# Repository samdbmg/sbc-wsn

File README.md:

# Speckled Bushcricket Wireless Sensor Network
Wireless Sensor Network for Acoustic Monitoring of Speckled Bush Crickets

##Known Issues (Node)
* Assembled sensor node temperature and light level sensors are broken (heat damage possibly)
* Sensor node environment sensors will require creative mounting for light and RH to be exposed outside. Suggest modifying onto an external header to another board (would also solve above problem)

##Known Issues (Base)
* GSM Modem doesn't currently execute HTTP requests, an error returns after setting the URL
* Base unit sometimes doesn't wake up at same time as node. Fitting a crystal to the Discovery board and switching RTC to the external 32k oscillator may help
* Power supplies start and generate stable output, however destroy regulator ICs after Discovery board is connected. Recommend thorough design review
* Discovery board will not fit unless headphone connector and button caps are removed. Suggest reworking to flip board, so Discovery fits on top and modem on bottom

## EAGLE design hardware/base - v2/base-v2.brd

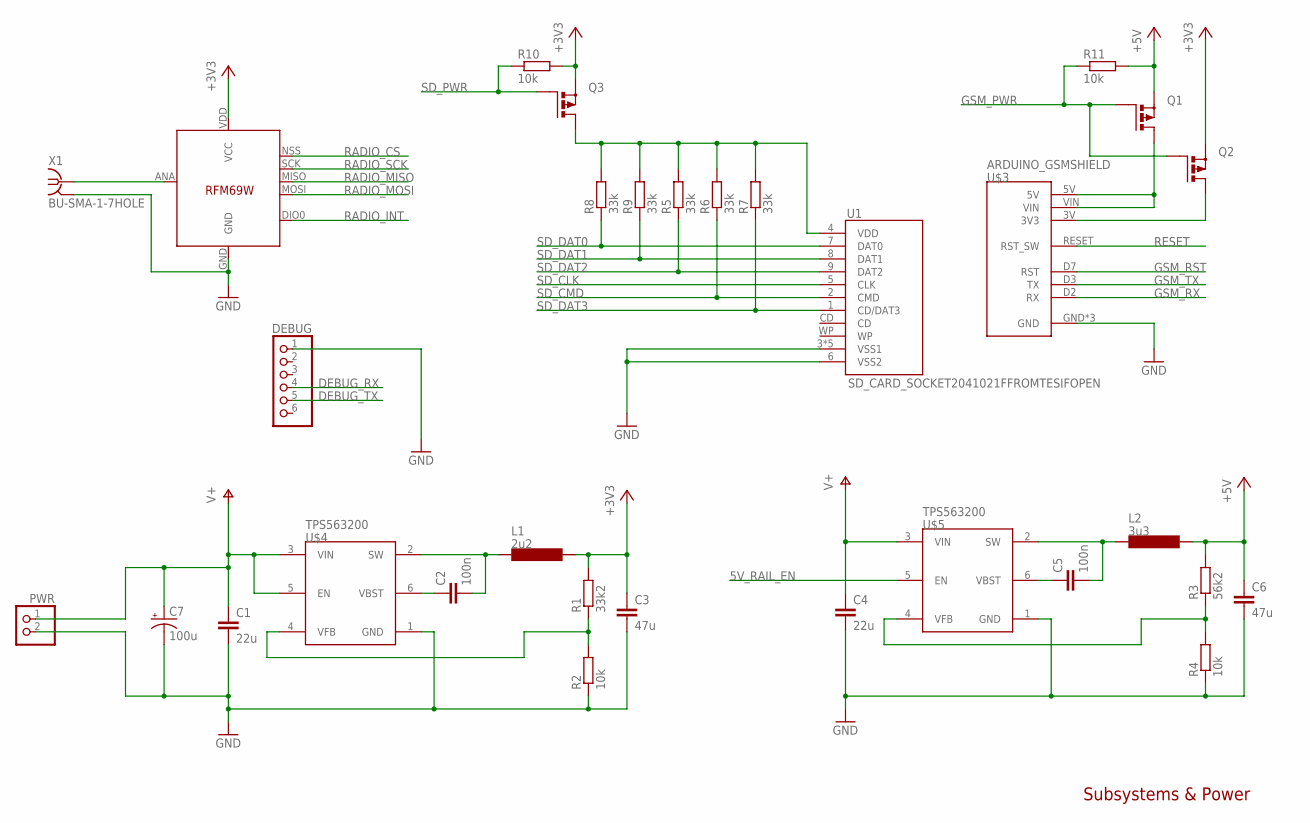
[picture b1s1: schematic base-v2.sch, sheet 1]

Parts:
C1, C4: 22u; 1206
C2, C5: 100n; CAP-PTH-SMALL
C3, C6: 47u; 1206
C7: 100u; CPOL-RADIAL-10UF-25V
DEBUG: PINHD-1X6; 1X06
L1: 2u2; SRR7032
L2: 3u3; SRR7032
PWR: PINHD-1X2; 1X02
Q1, Q2, Q3: PMOSFET_PTO220BH; TO220BH
R1: 33k2; 0204/7
R2, R4, R10, R11: 10k; 0204/7
R3: 56k2; 0204/7
R5, R6, R7, R8, R9: 33k; 0204/7
U1: SD_CARD_SOCKET2041021FFROMTESIFOPEN; SDCARD_2041021-3
U$2: RFM69; RFM69W-MINPADS
U$3: ARDUINO_GSMSHIELD; ARDUINO-NOHOLE
U$4, U$5: TPS563200; DDC0006A
X1: BU-SMA-1-7HOLE; SMA_1-7HOLES

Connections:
5V_RAIL_EN: U$5.5 (EN); also elsewhere on the board
+3V3: C3.1, L1.2, Q2.S, Q3.S, R1.2, R10.2, U$2.VDD (VCC); also elsewhere on the board
+5V: C6.1, L2.2, Q1.S, R3.2, R11.2; also elsewhere on the board
DEBUG_RX: DEBUG.4; also elsewhere on the board
DEBUG_TX: DEBUG.5; also elsewhere on the board
GND: C1.2, C3.2, C4.2, C6.2, C7.2 (-), DEBUG.1, PWR.2, R2.1, R4.1, U1.3 (VSS1), U1.6 (VSS2), U1.SH1 (VSS1), U1.SH2 (VSS1), U1.SH3 (VSS1), U1.SH4 (VSS1), U$2.GND, U$3.GND, U$3.GND1 (GND), U$3.GND2 (GND), U$4.1 (GND), U$5.1 (GND), X1.2, X1.3 (2), X1.4 (2), X1.5 (2); also elsewhere on the board
GSM_PWR: Q1.G, Q2.G, R11.1; also elsewhere on the board
GSM_RST: U$3.D7 (RST); also elsewhere on the board
GSM_RX: U$3.D2 (RX); also elsewhere on the board
GSM_TX: U$3.D3 (TX); also elsewhere on the board
unnamed: Q1.D, U$3.5V, U$3.VIN
unnamed: Q2.D, U$3.3V (3V3)
RADIO_ANT: U$2.ANA (ANT), X1.1
RADIO_CS: U$2.NSS (SEL); also elsewhere on the board
RADIO_INT: U$2.DIO0; also elsewhere on the board
RADIO_MISO: U$2.MISO; also elsewhere on the board
RADIO_MOSI: U$2.MOSI; also elsewhere on the board
RADIO_SCK: U$2.SCK; also elsewhere on the board
RESET: U$3.RESET (RST_SW); also elsewhere on the board
SD_CLK: U1.5 (CLK); also elsewhere on the board
SD_CMD: R6.1, U1.2 (CMD); also elsewhere on the board
SD_DAT0: R8.1, U1.7 (DAT0); also elsewhere on the board
SD_DAT1: R9.1, U1.8 (DAT1); also elsewhere on the board
SD_DAT2: R5.1, U1.9 (DAT2); also elsewhere on the board
SD_DAT3: R7.1, U1.1 (CD/DAT3); also elsewhere on the board
SD_PWR: Q3.G, R10.1; also elsewhere on the board
SD_VCC: Q3.D, R5.2, R6.2, R7.2, R8.2, R9.2, U1.4 (VDD)
V+: C1.1, C4.1, C7.1 (+), PWR.1, U$4.3 (VIN), U$4.5 (EN), U$5.3 (VIN)
VREG_3_SW: C2.2, L1.1, U$4.2 (SW)
VREG_3_VBST: C2.1, U$4.6 (VBST)
VREG_3_VFB: R1.1, R2.2, U$4.4 (VFB)
VREG_5_SW: C5.2, L2.1, U$5.2 (SW)
VREG_5_VBST: C5.1, U$5.6 (VBST)
VREG_5_VFB: R3.1, R4.2, U$5.4 (VFB)

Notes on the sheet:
Subsystems & Power

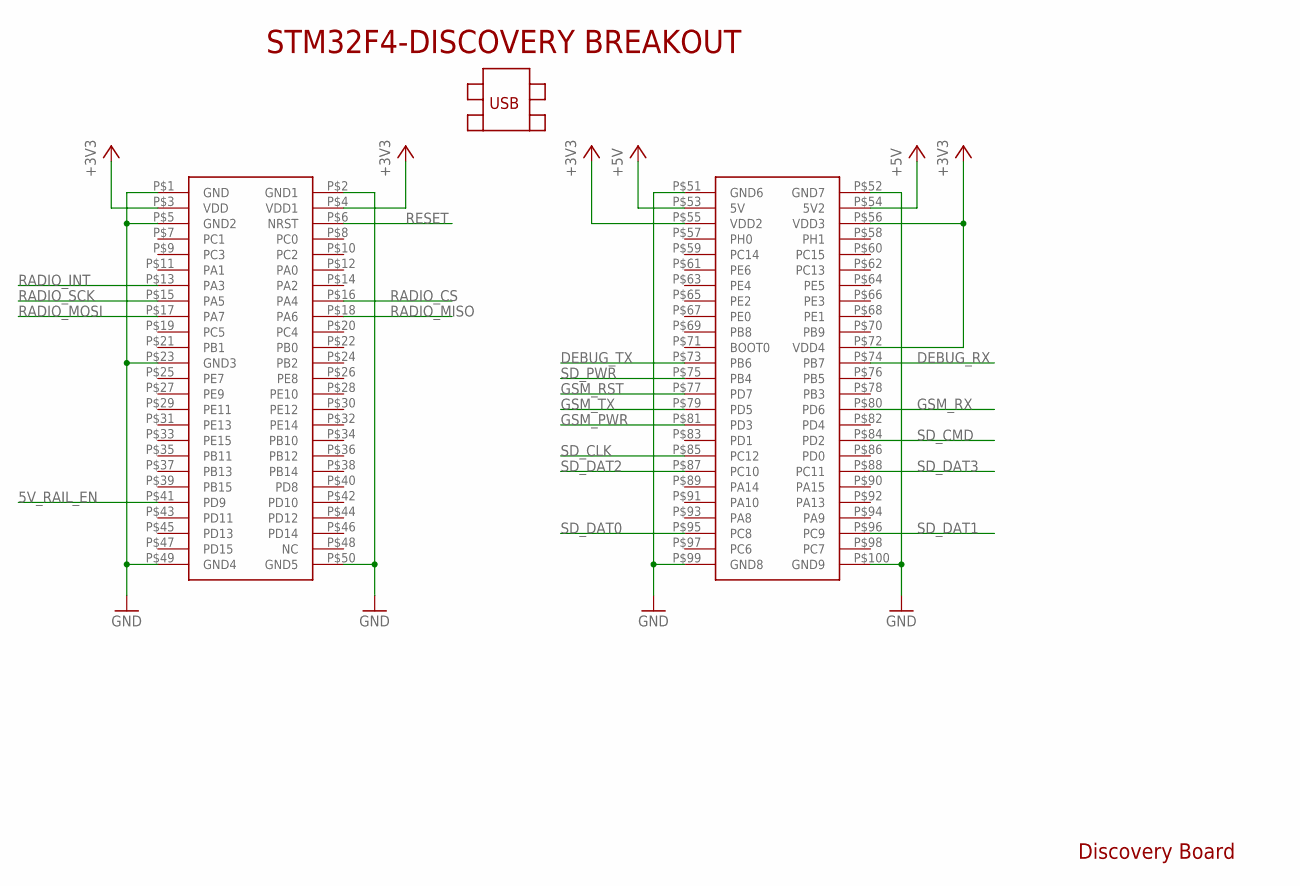
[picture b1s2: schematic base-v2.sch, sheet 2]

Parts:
U$1: STM32F4-DISCOVERY

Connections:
5V_RAIL_EN: U$1.P$41 (PD9); also elsewhere on the board
+3V3: U$1.P$3 (VDD), U$1.P$4 (VDD1), U$1.P$55 (VDD2), U$1.P$56 (VDD3), U$1.P$72 (VDD4); also elsewhere on the board
+5V: U$1.P$53 (5V), U$1.P$54 (5V2); also elsewhere on the board
DEBUG_RX: U$1.P$74 (PB7); also elsewhere on the board
DEBUG_TX: U$1.P$73 (PB6); also elsewhere on the board
GND: U$1.P$1 (GND), U$1.P$2 (GND1), U$1.P$5 (GND2), U$1.P$23 (GND3), U$1.P$49 (GND4), U$1.P$50 (GND5), U$1.P$51 (GND6), U$1.P$52 (GND7), U$1.P$99 (GND8), U$1.P$100 (GND9); also elsewhere on the board
GSM_PWR: U$1.P$81 (PD3); also elsewhere on the board
GSM_RST: U$1.P$77 (PD7); also elsewhere on the board
GSM_RX: U$1.P$80 (PD6); also elsewhere on the board
GSM_TX: U$1.P$79 (PD5); also elsewhere on the board
RADIO_CS: U$1.P$16 (PA4); also elsewhere on the board
RADIO_INT: U$1.P$13 (PA3); also elsewhere on the board
RADIO_MISO: U$1.P$18 (PA6); also elsewhere on the board
RADIO_MOSI: U$1.P$17 (PA7); also elsewhere on the board
RADIO_SCK: U$1.P$15 (PA5); also elsewhere on the board
RESET: U$1.P$6 (NRST); also elsewhere on the board
SD_CLK: U$1.P$85 (PC12); also elsewhere on the board
SD_CMD: U$1.P$84 (PD2); also elsewhere on the board
SD_DAT0: U$1.P$95 (PC8); also elsewhere on the board
SD_DAT1: U$1.P$96 (PC9); also elsewhere on the board
SD_DAT2: U$1.P$87 (PC10); also elsewhere on the board
SD_DAT3: U$1.P$88 (PC11); also elsewhere on the board
SD_PWR: U$1.P$75 (PB4); also elsewhere on the board

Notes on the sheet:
Discovery Board

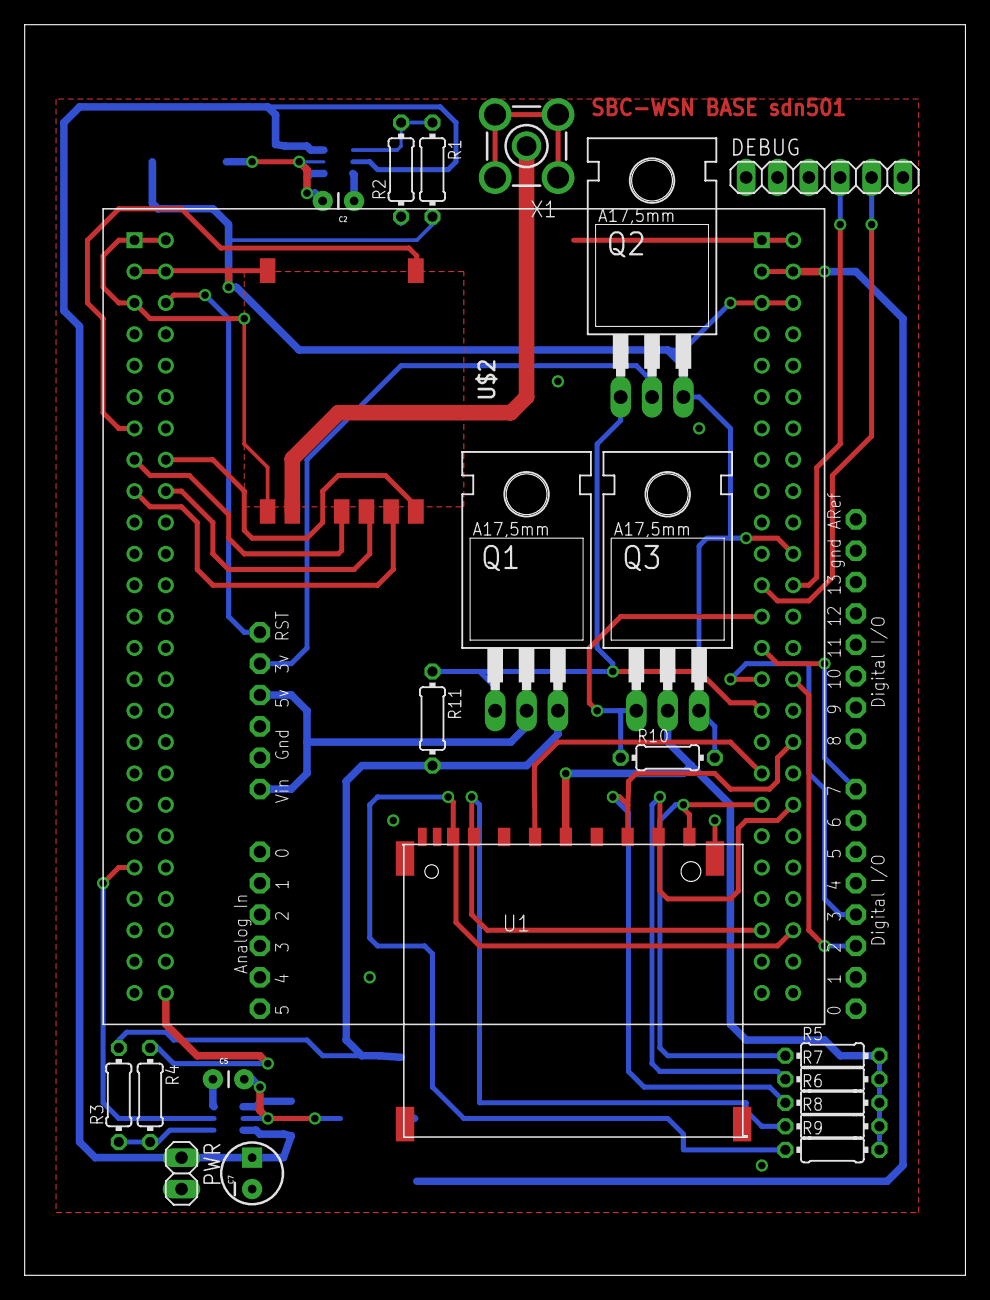
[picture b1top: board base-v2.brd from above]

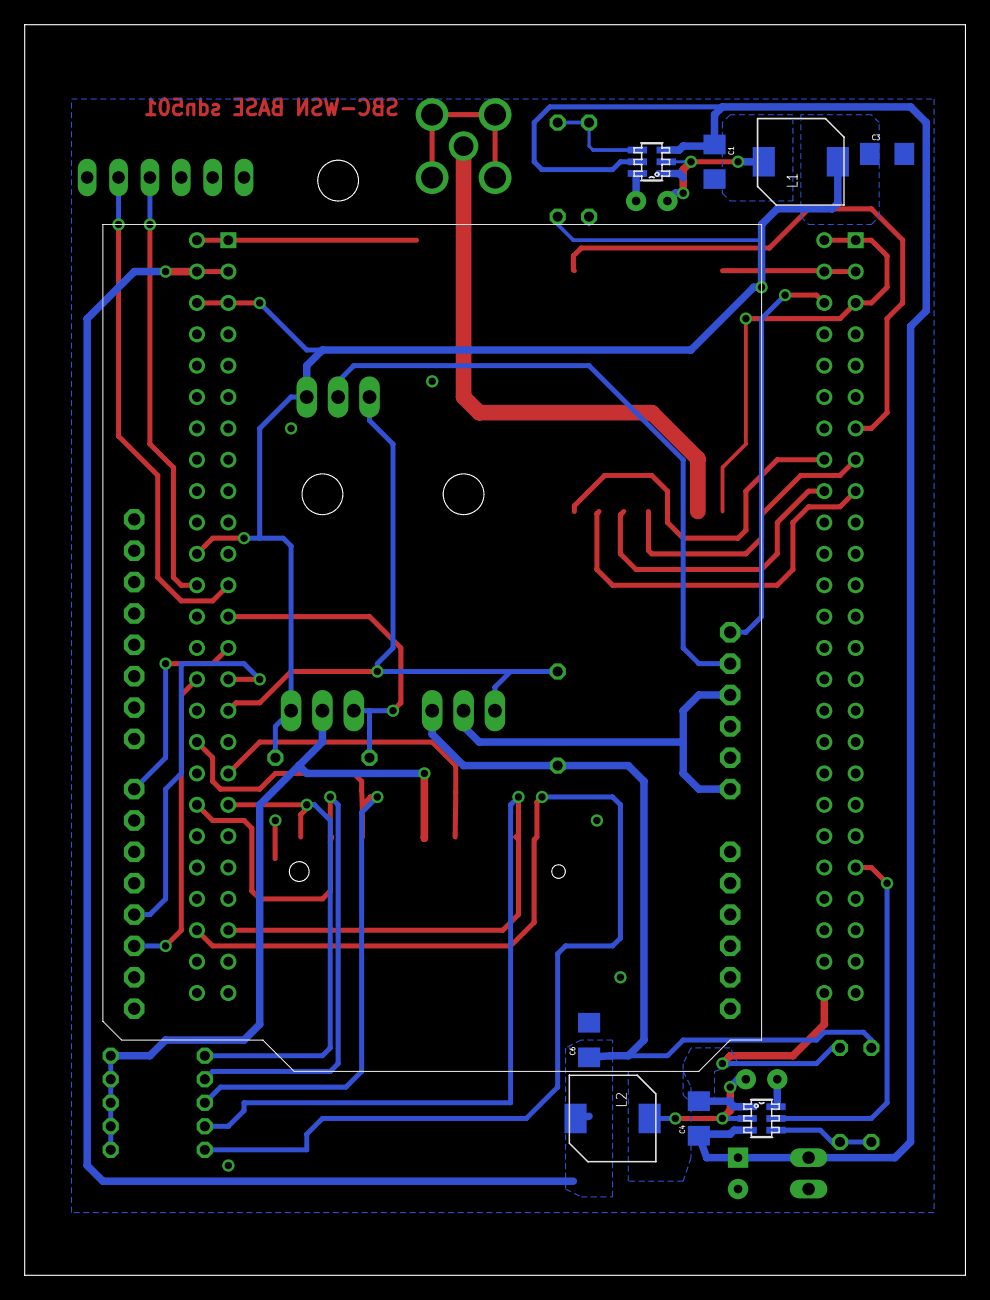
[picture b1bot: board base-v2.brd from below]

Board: 2 copper layers, 76.2 x 101.3 mm, 32 parts (8 on the bottom side), 34 nets.

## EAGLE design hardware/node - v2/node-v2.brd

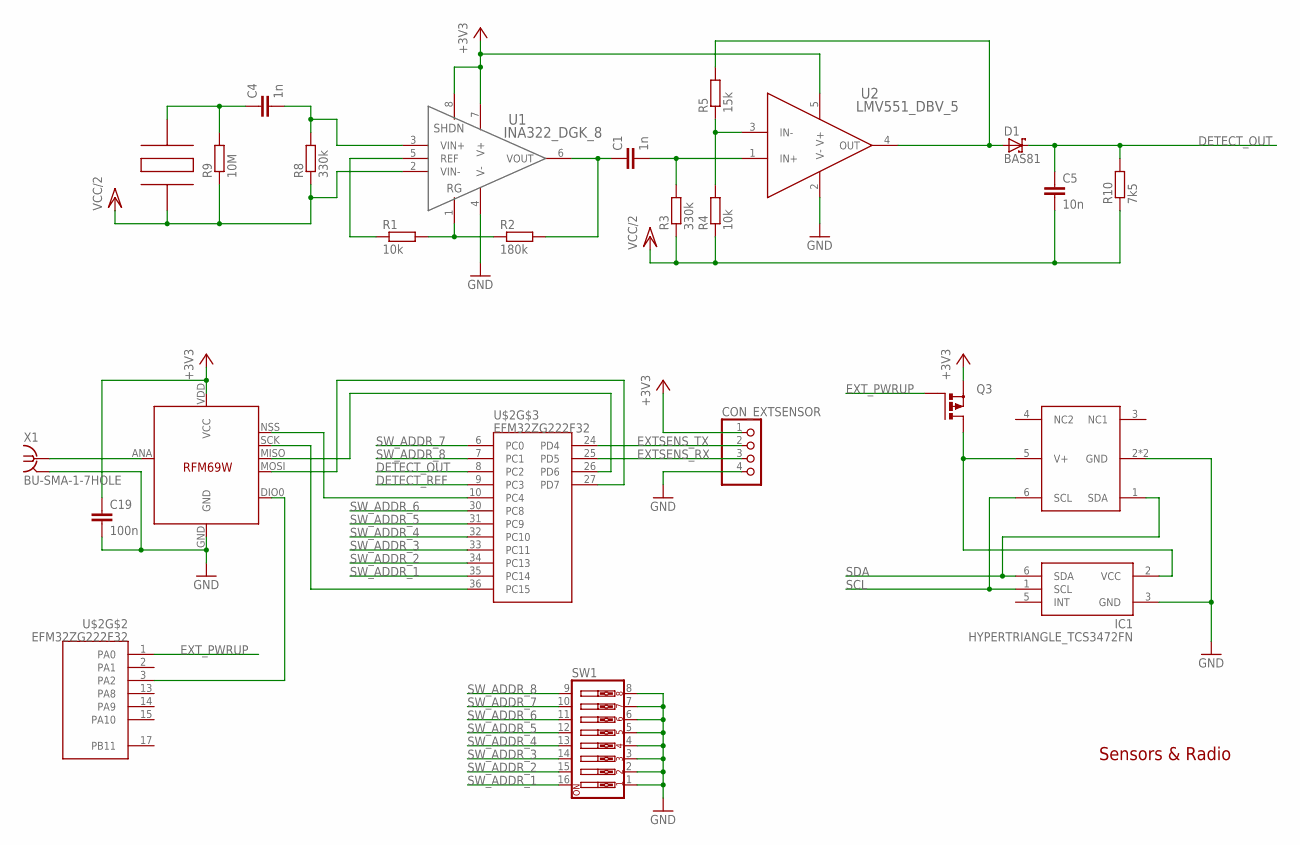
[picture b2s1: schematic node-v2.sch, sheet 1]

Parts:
C1, C4: 1n; CAP-PTH-SMALL
C5: 10n; CAP-PTH-SMALL
C19: 100n; CAP-PTH-SMALL
CON_EXTSENSOR: PINHD-1X4; 1X04
D1: BAS81; DO35-7
IC1: HYPERTRIANGLE_TCS3472FN; HYPERTRIANGLE_DFN-6
Q3: PMOSFET_PTO220BH; TO220BH
R1, R4: 10k; 0204/7
R2: 180k; 0204/7
R3, R8: 330k; 0204/7
R5: 15k; 0204/7
R9: 10M; 0204/7
R10: 7k5; 0204/7
RADIO: RFM69; RFM69W-MINPADS
SW1: SW_DIP-8; DIPSWITCH-08
U1: INA322_DGK_8; DGK8
U2: LMV551_DBV_5; MF05A
U$1: PIEZOWIREHEADER; 1X02
U$2: EFM32ZG222F32; QFP48
U$3: SHT21
X1: BU-SMA-1-7HOLE; SMA_1-7HOLES

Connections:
+3V3: C19.1, CON_EXTSENSOR.1, Q3.S, RADIO.VDD (VCC), U1.7 (V+), U1.8 (SHDN), U2.5 (V+); also elsewhere on the board
DETECT_OUT: C5.1, D1.C, R10.2, U$2.8 (PC2)
DETECT_REF: U$2.9 (PC3); also elsewhere on the board
EXTSENS_RX: CON_EXTSENSOR.3, U$2.25 (PD5)
EXTSENS_TX: CON_EXTSENSOR.2, U$2.24 (PD4)
EXT_PWRLINE: IC1.2 (VCC), Q3.D, U$3.5 (V+)
EXT_PWRUP: Q3.G, U$2.1 (PA0)
GND: C19.2, CON_EXTSENSOR.4, IC1.3 (GND), RADIO.GND, SW1.1, SW1.2, SW1.3, SW1.4, SW1.5, SW1.6, SW1.7, SW1.8, U1.4 (V-), U2.2 (V-), U$3.2 (GND), U$3.P$1 (GND), X1.2, X1.3 (2), X1.4 (2), X1.5 (2); also elsewhere on the board
INSTR_FILTERED: C1.2, R3.2, U2.1 (IN+)
INSTR_OUT: C1.1, R2.2, U1.6 (VOUT)
unnamed: RADIO.MISO, U$2.26 (PD6)
OPAMP_OUT: D1.A, R5.2, U2.4 (OUT)
OPAMP_VGND: R4.2, R5.1, U2.3 (IN-)
PIEZO_FILTERED: C4.2, R8.2, U1.3 (VIN+)
PIEZO_OUT: C4.1, R9.2, U$1.1 (S+)
RADIO_ANT: RADIO.ANA (ANT), X1.1
RADIO_CS: RADIO.NSS (SEL), U$2.10 (PC4)
RADIO_INT: RADIO.DIO0, U$2.3 (PA2)
RADIO_MOSI: RADIO.MOSI, U$2.27 (PD7)
RADIO_SCK: RADIO.SCK, U$2.36 (PC15)
REFLINE: R1.1, U1.5 (REF)
RGLINE: R1.2, R2.1, U1.1 (RG)
SCL: IC1.1 (SCL), U$3.6 (SCL); also elsewhere on the board
SDA: IC1.6 (SDA), U$3.1 (SDA); also elsewhere on the board
SW_ADDR_1: SW1.16, U$2.35 (PC14)
SW_ADDR_2: SW1.15, U$2.34 (PC13)
SW_ADDR_3: SW1.14, U$2.33 (PC11)
SW_ADDR_4: SW1.13, U$2.32 (PC10)
SW_ADDR_5: SW1.12, U$2.31 (PC9)
SW_ADDR_6: SW1.11, U$2.30 (PC8)
SW_ADDR_7: SW1.10, U$2.6 (PC0)
SW_ADDR_8: SW1.9, U$2.7 (PC1)
VCC/2: C5.2, R3.1, R4.1, R8.1, R9.1, R10.1, U1.2 (VIN-), U$1.2 (S-); also elsewhere on the board

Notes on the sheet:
Sensors & Radio

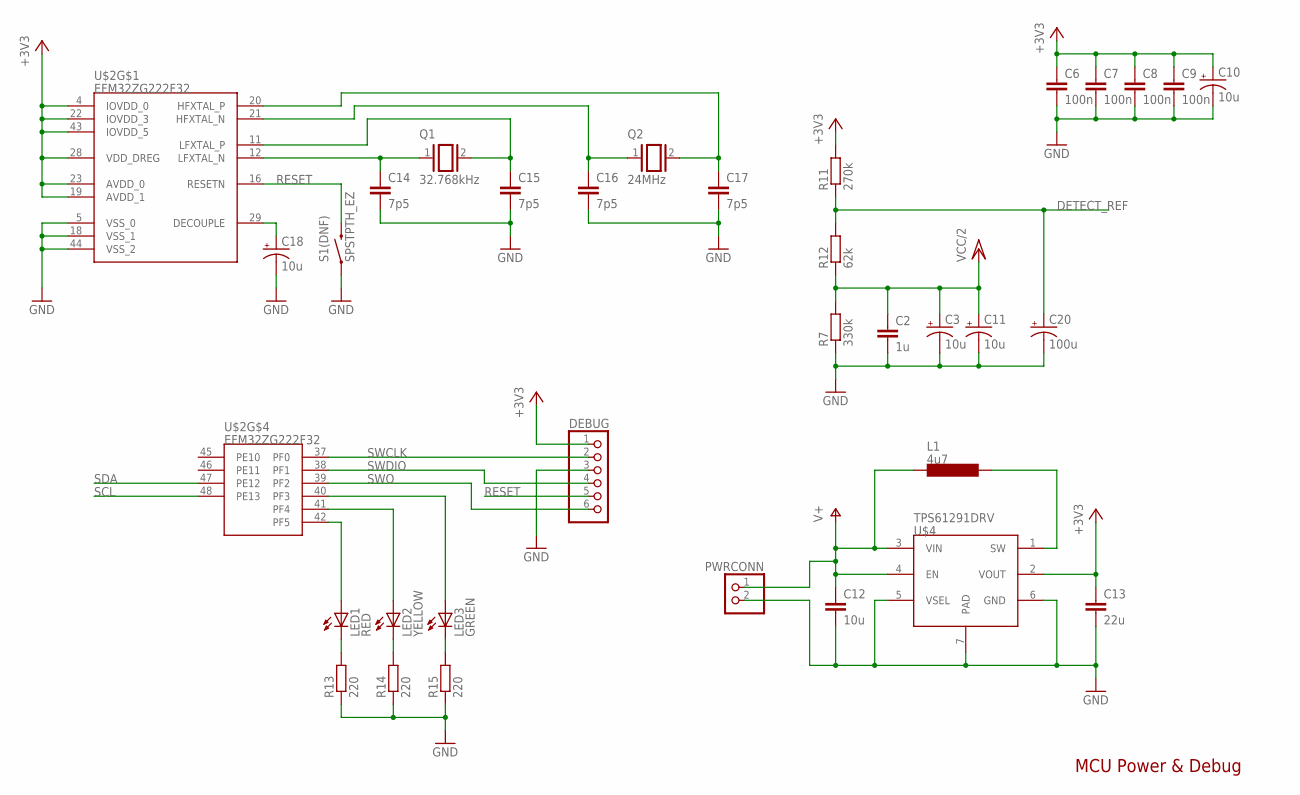
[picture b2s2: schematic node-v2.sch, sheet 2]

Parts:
C2: 1u; CAP-PTH-SMALL
C3, C10, C11, C18: 10u; CPOL-RADIAL-10UF-25V
C6, C8, C9: 100n; CAP-PTH-SMALL
C7: 100n; CAP-PTH-5MM
C12: 10u; 1206
C13: 22u; 1206
C14, C15, C16, C17: 7p5; CAP-PTH-SMALL
C20: 100u; CPOL-RADIAL-10UF-25V
DEBUG: PINHD-1X6; 1X06
L1: 4u7; LTF5022
LED1: RED; LED3MM
LED2: YELLOW; LED3MM
LED3: GREEN; LED3MM
PWRCONN: PINHD-1X2; 1X02
Q1: 32.768kHz; QS
Q2: 24MHz; QS
R7: 330k; 0204/7
R11: 270k; 0204/7
R12: 62k; 0204/7
R13, R14, R15: 220; 0204/7
S1(DNF): SPSTPTH_EZ; TACTILE-PTH-EZ
U$2: EFM32ZG222F32; QFP48
U$4: TPS61291DRV; DRV0006A

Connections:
+3V3: C6.1, C7.1, C8.1, C9.1, C10.1 (+), C13.1, DEBUG.1, R11.2, U$2.4 (IOVDD_0), U$2.19 (AVDD_1), U$2.22 (IOVDD_3), U$2.23 (AVDD_0), U$2.28 (VDD_DREG), U$2.43 (IOVDD_5), U$4.2 (VOUT); also elsewhere on the board
DECOUPLE: C18.1 (+), U$2.29 (DECOUPLE)
DETECT_REF: C20.1 (+), R11.1, R12.2; also elsewhere on the board
GND: C2.2, C3.2 (-), C6.2, C7.2, C8.2, C9.2, C10.2 (-), C11.2 (-), C12.2, C13.2, C14.2, C15.2, C16.2, C17.2, C18.2 (-), C20.2 (-), DEBUG.3, PWRCONN.2, R7.1, R13.1, R14.1, R15.1, S1(DNF).1, U$2.5 (VSS_0), U$2.18 (VSS_1), U$2.44 (VSS_2), U$4.5 (VSEL), U$4.6 (GND), U$4.7 (PAD); also elsewhere on the board
LED_GREEN: LED3.A, U$2.40 (PF3)
LED_RED: LED1.A, U$2.42 (PF5)
LED_YELLOW: LED2.A, U$2.41 (PF4)
LFXTAL_N: C15.1, Q1.2, U$2.11 (LFXTAL_P)
LFXTAL_P: C14.1, Q1.1, U$2.12 (LFXTAL_N)
unnamed: LED1.K (C), R13.2
unnamed: LED2.K (C), R14.2
unnamed: LED3.K (C), R15.2
RESET: DEBUG.5, S1(DNF).3 (2), U$2.16 (RESETN)
SCL: U$2.48 (PE13); also elsewhere on the board
SDA: U$2.47 (PE12); also elsewhere on the board
SWCLK: DEBUG.2, U$2.37 (PF0)
SWDIO: DEBUG.4, U$2.38 (PF1)
SWO: DEBUG.6, U$2.39 (PF2)
V+: C12.1, L1.1, PWRCONN.1, U$4.3 (VIN), U$4.4 (EN)
VCC/2: C2.1, C3.1 (+), C11.1 (+), R7.2, R12.1; also elsewhere on the board
VREG_SW: L1.2, U$4.1 (SW)
XTALN: C17.1, Q2.2, U$2.20 (HFXTAL_P)
XTALP: C16.1, Q2.1, U$2.21 (HFXTAL_N)

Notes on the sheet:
MCU Power & Debug

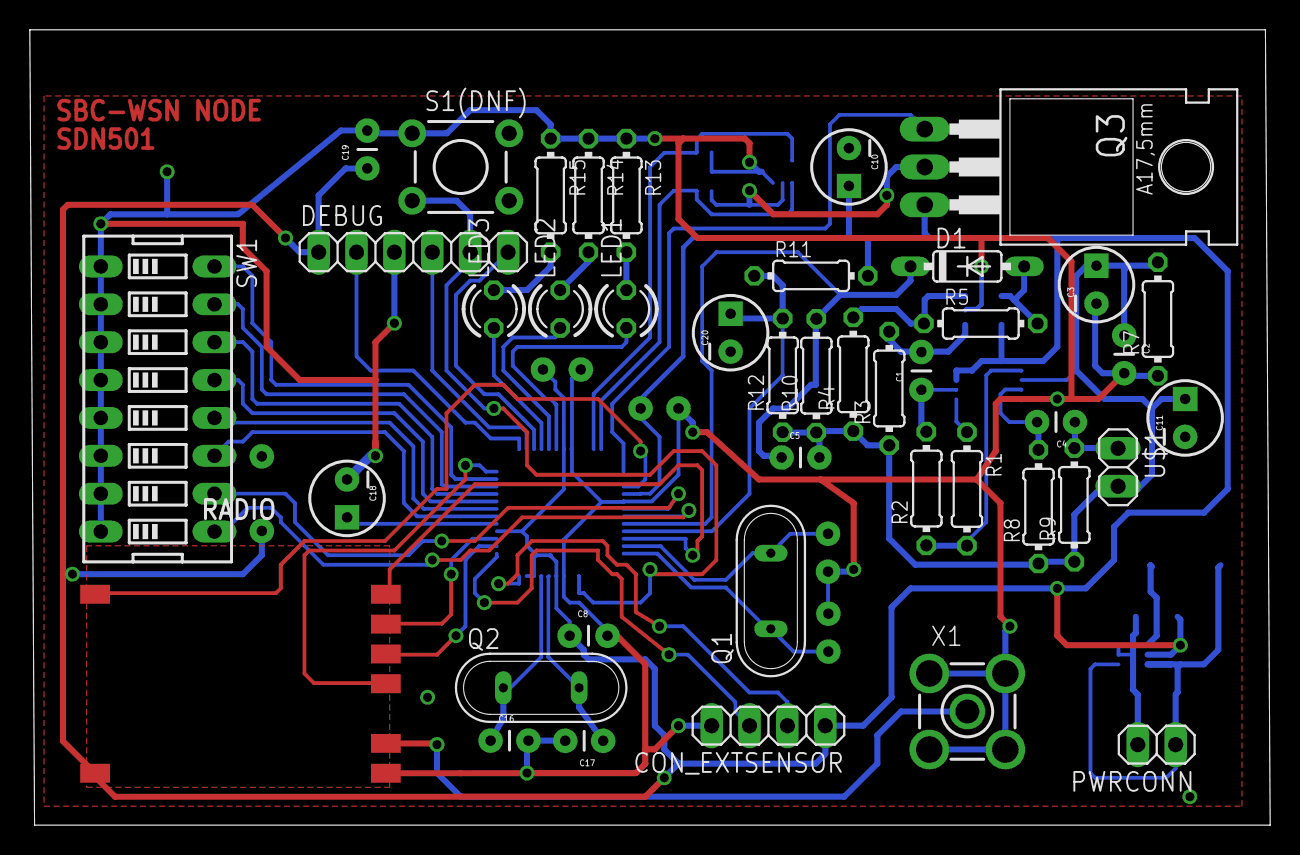
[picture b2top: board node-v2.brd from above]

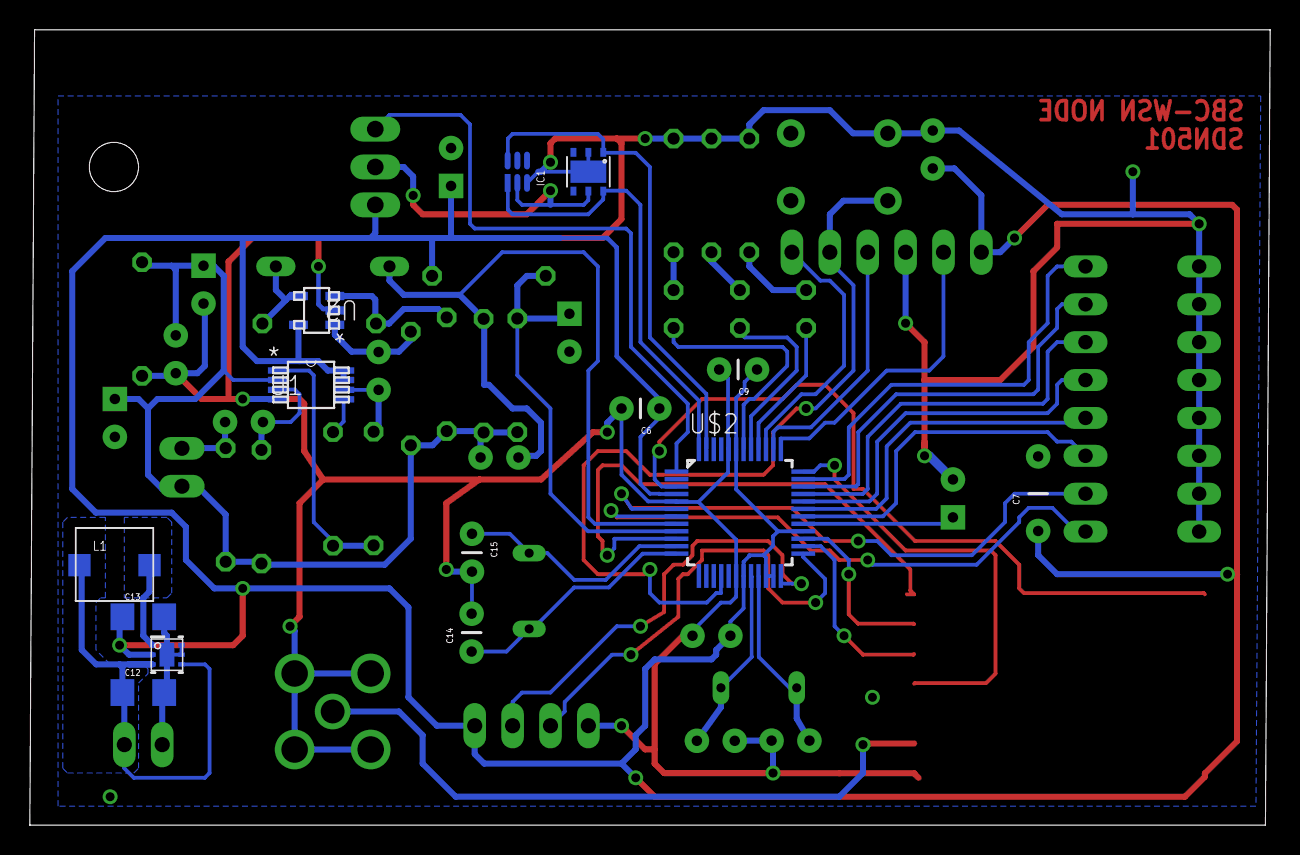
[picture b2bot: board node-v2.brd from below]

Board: 2 copper layers, 83.2 x 53.3 mm, 56 parts (14 on the bottom side), 50 nets.

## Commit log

2015-01-12 Updated README to include a better title
2015-01-12 Added initial artificial-cricket code project
2015-01-12 Wrote some PWM init, switched to StdPeriph from HAL. Played with warnings
2015-01-12 Ignored Debug folder
2015-01-13 Minor fixes to make PWM generator work
2015-01-13 Artificial Cricket: Rejoice in the PWM cricket calls. No gaps or randomness yet
2015-01-13 Removed some extraneous debug stuff from last commit
2015-01-13 Now has a timer to make a call every second
2015-01-13 Used the proper OpenOCD debug method and made it reload on rerun
2015-01-13 AC: Set up semihosting so trace_printf() dumps to openocd console
2015-01-13 AC: Code cleanup and a header refactor
2015-01-13 AC: Random adjust and user switch code
2015-01-20 EFM32: Added simple ADC demo for EFM32 ZeroGecko
2015-01-20 Ignored out some more debug folders
2015-01-20 EFM32: Added RTC
2015-01-20 EFM32: Added untested SPI support
2015-01-20 Set some of the required flags to use SPI
2015-01-20 EFM32: Refactored to split ADC and pin change mode. Made pin change mode
2015-01-20 AC: Made random call count adjust work
2015-01-21 EFM32: ADC demo now reads ADC data and actually sends it on SPI without waiting
2015-01-21 EFM32: PCNT performance is inadequate
2015-01-21 Pinchange got a complete rethink, works now!
2015-01-22 EFM32: Wrote a detection algorithm, it might work...
2015-01-26 Disabled semihosting (unstable) and reconfigured to be suited for algorithm initial testing
2015-01-26 Made detection algorithm actually work!
2015-01-26 Removed semihosting on account of it being broken
2015-01-27 Algorithm makes heavier use of interrupts, may be more reliable
2015-01-28 EFM32: Algorithm is now markedly more forgiving and generally better
2015-01-28 AC: Turned the auto signalling back on
2015-01-29 CC430: Added simple CC430 node demo
2015-01-30 AC: Made call timer activation configurable, added debounce on trigger switch (very simple!)
2015-01-30 CC430: Set some release mode configurations
2015-01-30 Updated ignore file to include new CC430 project
2015-01-30 CC430: Implemented algorithm for CC430 (no RTC yet)
2015-02-13 RFM69W: Added RFM69W Arduino code
2015-02-19 AC: Turned off semihosting
2015-03-04 CC430: I appear to have fiddled to try and make range better. Didn't help much!
2015-03-04 Archived some old projects, added remaining archive folder to ignore
2015-03-04 Added battery power calculator tool
2015-03-04 Node: Added some skeleton node software
2015-03-04 Fixed ignores to remove node software debug folder
2015-03-05 Node: In principle the detection algorithm is implemented with the comparator
2015-03-05 NODE: Added a note about where ACMP code came from, formatted to match style
2015-03-05 NODE: Radio control boilerplate written, checks communications but doesn't configure yet
2015-03-05 NODE: Modified how radio powerdown works to actually put radio to low power mode
2015-03-05 NODE: Added beginnings of configuration set, now need to set all registers
2015-03-06 AC: Added female responses to calls. Disabled auto-update to try and stabilise debugger
2015-03-08 NODE: Quite a few important components had been turned off by mistake (cough cough timers)
2015-03-08 NODE: Main file gets a vigorous trim and set up for radio testing
2015-03-08 NODE: Radio now configures on startup (and responds!). Lights an LED if radio setup fails
2015-03-10 NODE: Detect algorithm gets hits, still doesn't work!
2015-03-10 Removed a built file that accidentally made it into repo
2015-03-10 NODE: Radio TX works in principle, some RX skeleton code written. Still needs rest of RX interrupt handler writing, plus configuration data (paying particular attention to ensure listen wake will alw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
2015-03-11 NODE: Detection algorithm now spots large numbers of transients in a call and rejects it, doesn't pick up my keys as a valid call. Some tuning of thresholds done, detect algorithm generally fixed
2015-03-11 NODE: Made some macros a bit better with brackets courtesy CCL's interviewers
2015-03-11 Prevented the randomness algorithm for generating 4-click calls
2015-03-11 NODE: Wrote some power management code
2015-03-15 NODE: Wrote remaining radio config and setup code
2015-03-15 NODE: Made radio send a single test packet, wait for receive complete interrupt
2015-03-15 NODE: Removed some radio debug code
2015-03-15 NODE: Improved detect power draw down to 3uA
2015-03-15 NODE: Added energyAware tool files
2015-03-15 NODE: Added some sensor interface code. Doesn't work mind!
2015-03-16 NODE: Ringbuffers made better, config fixed to match Arduino, radios work!
2015-03-16 RFM69W-ARDUINO: Made it work a bit better with Gecko code
2015-03-16 NODE: Remembered how I2C addresses work, fixed temp and RH sensors
2015-03-16 NODE: Finished fixing sensors
2015-03-17 Code standardisation and cleanup
2015-03-17 NODE: Some code cleanup as a side effect of using more stringent STM32 compiler, plus made receive mode on radios re-assert if it was active before a transmit started
2015-03-17 BASE: Added initial project. Note that radio_control.h/c and radio_config.h are all symlinked to their node software counterparts so .ignored as git doesn't understand
2015-03-17 AC: Fixed the problem with the debugger disconnecting - turns out it does that if the CPU sleeps
2015-03-17 BASE: Prevented code continuing if radio startup failed, made debug work
2015-03-17 BASE: Added serial debug out
2015-03-17 BASE: Fixed SPI...sometimes
2015-03-19 NODE+BASE: Added function scheduling and made some power management improvements, prevented nested radio interrupts
2015-03-19 BASE: Made radio TX/RX work reliably, set some more sensible clocks
2015-03-19 NODE: Made radio send/receive work reliably
2015-03-19 NODE: Wrote a simple RTC driver (untested)
2015-03-22 NODE: Tested the RTC driver, made the code a little more user friendly
2015-03-22 NODE: Added a detect data storage class and made the detect algorithm write to it
2015-03-24 BASE: Wrote output stuff to display radio data on console
2015-03-24 NODE: Periodic update to base partly works
2015-04-01 BASE: Added better debugging from an embedded printf() library
2015-04-01 NODE: Fixed some of the off by one errors in ringbuffers and packets
2015-04-01 NODE: Added timeout on transmit wait function, made power sleep scheduling slightly more reentrant
2015-04-01 BOTH: Clock can now be updated from base node
2015-04-01 BOTH: Moved MSB of time into type byte
2015-04-01 NODE: Cleaned up clock initialisation routines
2015-04-01 AC: Generates serial data for external interface
2015-04-01 NODE: Reads data from external interface and sends
2015-04-01 Rethought how the datastore works to be a ringbuffer, made some other stuff better, repeats might work...
2015-04-04 NODE: Minor delay function clarification
2015-04-04 BOTH: Migrated radio stuff to their own files rather than main.c, made roughly work with single packets
2015-04-05 NODE: Datastore is all in bytes
2015-04-05 BASE: Fixed a lot of radio protocol bugs, now actually fragments/assembles/ARQs
2015-04-05 NODE: Radio now responds to repeats properly
2015-04-06 NODE: Updates Simplicity Studio to v3
2015-04-07 BASE: Found and integrated an SD card library
2015-04-10 NODE: Minor data store comment typofix
2015-04-10 BASE: Replaced printf library with one supporting sprintf
2015-04-10 BASE: Added misc code for ringbuffer functionality, delays
2015-04-10 BASE: Added some broken GSM code
2015-04-10 NODEHW: Added schematic for analog bits, EAGLE project
2015-04-10 NODEHW: Added MCU power
2015-04-10 NODE: Added radio
2015-04-10 NODE: Added sensors, power control
2015-04-11 NODEHW: Added EFM32 pinout document
2015-04-11 NODEHW: Finished first schematic draft
2015-04-11 BASEHW: Schematic mostly done
2015-04-13 BASEHW: Added missing power bits, basically done now
2015-04-13 NODEHW: Schematic basically finished
2015-04-15 NODEHW: Some components placed...
2015-04-15 NODEHW: Routeing starts
2015-04-15 NODEHW: Routeing ongoing
2015-04-15 NODEHW: Routed the switch stuff sortof
2015-04-15 NODEHW: Routeing rethought, bettered
2015-04-16 NODEHW: NODE ROUTING FINISHED!!! YAYYYY!
2015-04-17 NODEHW: Tweaks to line up LEDs, fix DRC issues
2015-04-17 NODEHW: Updated ignore file to remove autorouter data
2015-04-17 NODE: Added some lines for debug
2015-04-17 Finished off routeing by fixing some stuff
2015-04-19 BASEHW: Radio routed
2015-04-19 NODEHW: PSU layout now looks like TI's
2015-04-19 BASEHW: Yayy, hardware design done
2015-04-20 BASEHW: Pass for layout bugs, SD pullups
2015-04-20 NODEHW: Layout cleanup. Also added base text
2015-04-20 NODEHW: Added text label
2015-04-20 NODEHW: New inductor
2015-04-20 BASEHW: New inductors, larger resistors
2015-04-21 BASEHW: New SD footprint
2015-04-21 NODEHW: Changed transistor package, changed caps to SMD
2015-04-21 NODEHW: Sent for fab
2015-04-21 BASEHW: Replaced PSU caps with 1206 parts, added transistor to make MOSFETs work with VREG
2015-04-21 Fixed bad transistor setup
2015-04-21 BASEHW: Board sent for MFR
2015-04-23 RadioCode: The upshot of hardcore radiofix day
2015-04-23 Radio: Fixed a receive bug, data usually makes it, most of the time
2015-04-23 AC: Fixed to different thingbats
2015-04-23 NODE: Female detection implemented, works (tested)
2015-04-27 NODE: LED Status is now a thing
2015-04-27 NODE: Address lookup from switches
2015-04-29 BASE: Fiddle radio code to add delay before ACK, works better now
2015-04-29 NODE: Changes to work with real hardware
2015-04-29 Tried to do RTC on discovery board. Doesn't.
2015-05-13 Commit before submit
2015-05-19 NODE: Added LEUART output of debug messages. Closes #7
2015-05-19 NODE: Added a short delay between sending I2C and waiting for responses, which appears to fix the lockup in sensor setup found with the debugger disconnected (and resulting timing changes). Fixes #5
2015-05-19 NODEHW: Started updates for V2 design
2015-05-20 NODE: Failure of i2c sensor startup now causes a timeout and an error rather than a lockup. Partially related to #5
2015-05-20 NODE: Added some debugging to the detect algorithm in an attempt to fix #10
2015-05-20 NODE: Neatened up some of the detect algorithm reset code as part of #10
2015-05-20 NODE: Added more debug statements to radio protocol
2015-05-20 NODEHW: Further updates to capacitor values found as part of #6
2015-05-20 BASE: Untested changes made in pursuit of a solution to #3
2015-05-21 NODE: Fixed bugs in detection algorithm. Fixes #10
2015-05-22 AC: Timings adjusted, fixed a bug where random adjust breaks if female is off
2015-05-22 BOTH: Fixed a radio setup failure bug due to power supply instability
2015-05-22 NODE: Removed test code to upload sample data on radio
2015-05-22 BOTH: Data are being detected and uploaded!
2015-05-22 NODE: Number of clicks is now stored
2015-05-22 AC: Fixed mark space to actually match real insect. Improved female handling on button push
2015-05-22 BASE: Now prints out whether a female was detected
2015-05-22 BASE: Added power control for modem, SD card
2015-05-23 BASE: Modified RTC code to fix #3
2015-05-23 BASE: Removed some test/debug lines
2015-05-23 BOTH: Partial fixes to the syncing problems
2015-05-23 BOTH: Tested/fixed schedule generation code (fixes #7) and also fixed RTC alarms (fixes #3) and finally set to name file by current date (fixes #2)
2015-05-23 NODEHW: Added list of modifications required for V1 hardware
2015-05-23 NODEHW: Completed v2 rework. There are no ADC pins available for #9 therefore it is wontfix.
2015-05-23 BASEHW: Completed base board rework
2015-05-23 Wrote up list of known issues
2015-05-24 AC: Added code to set speeds from ADC
2015-05-28 BASE: Minor fix to make schedule generation after startup work correctly

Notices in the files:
parts and their libraries:
SparkFun-Capacitors: Licensing: Creative Commons ShareAlike 4.0 International - https://creativecommons.org/licenses/by-sa/4.0
